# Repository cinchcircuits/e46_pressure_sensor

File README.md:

# BMW e46 pressure sensor
Boards and code for adding a pressure sensor to a BMW e46

This project adds a pressure and engine tempature readout to a BMW e46. 

# Desired install
This is the goal of the project:

The display reads out the current pressure from the installed pressure sensor, and reads \
out the engine temperature read from the CAN bus.

# Why read the temperature? 

# Board design
Find the board files [Here](board/i2c-pressure-sensor-driver)

The PCB uses the following components:
- [Teensy 4.0](https://www.pjrc.com/store/teensy40.html)
- [I2C Pressure sensor](https://www.newark.com/amphenol-advanced-sensors/npi-19m-200g2/pressure-sensor-200psi-gauge-i2c/dp/70AJ5206)
- [CAN bus tranciever](https://www.mouser.com/ProductDetail/579-MCP2562FD-E-SN)
- [wire attachment headers 4 pin](https://www.mouser.com/ProductDetail/571-1546215-4)
- [wire attachment headers 3 pin](https://www.mouser.com/ProductDetail/TE-Connectivity/282834-3?qs=A%252Bip%252BNCYi6M69kAjqV38yA%3D%3D)
- [Inexpensive "OLED" displays](https://www.amazon.com/gp/product/B08ZY4YBHL)
- [Inexpensive Amazon 3.3v relay](https://www.amazon.com/gp/product/B09P1DS8RN)
- [Shielded wire to carry the I2C](https://www.mouser.com/ProductDetail/602-M4473-100-09)

## Why an I2C pressure sensor? 

I was getting tired of dealing with analog output sensors that I was using in a different project.
So, I bought the I2C digital output sensor. It turned out to be really easy to read from.

The bad: The manufacturer lists the tread as having a M12 x 1.5 thread on it. That would be great, because that is what the sensor port on the e46 is. The problem is that these sensors actually ship with a M12 x 1.0 thread on it. 

So, I had to make an adapter for this sensor. I made it by buying one of these: [m12 to NPT adapter](https://www.amazon.com/gp/product/B08DG6YQM1)
I then threw the thing in my lathe, and cut off everything at the NPT hole and back. 
After that I bought a tap[m12 x 1.0 tap](https://www.amazon.com/gp/product/B07Z1WJ6XR)

I had to drill out the internal cavity just a bit, then I taped it and mounted the pressure sensor in the hole. Using teflon tape, and a Niton o-ring to make a seal. 

This is the result of the adapter:

## Board design

I had to rev the board once as I originally powered the 3.3v regulator off of the 12V rail, and that meant that nothing on the board got power when it wasn't plugged into an external voltage source. After moving the 3v3 regulator input to the 5V rail fixed that issue. 

I felt it was a bad idea to connect the teensy 3.3v rail to the main board 3.3v rail as that could mean that the teensy 3.3v regulator could get over currented if the relay came on when plugged into a USB connection. 

## Manufacturing the board

This time I used pcbway. They seem to have an amazing deal of $25 for a 5 boards in a 24 hour turn from China. Shipping takes a additional 5 busniess days though.

# Install

## pressure sensor install

- Start by removing the airbox
- That should give you access to the oil pressure switch, unplug it
- Unscrew the factory pressure switch
- Screw in the new pressure sensor (Perhaps with the adapter). Ideally you installed a connector in the cable unlike the way I did.
- Make some notches in the wire grommetsgoing to the DME to make room for the sensor cable

## Wire install to display

If you remove the DME completly you get access to a firewall passthrough hole in the e46, shown

Run about a meter of cable into the cabin

Pull the plastic cover off of the driver side footwell, to feed the wire through

Run the wire to the center console

You can pull on the shift boot to get at some screws to remove the center console panel

## Display mounting

I first drilled a hole in the button console where I wanted the display. Don't do that. 

Remove the button console completly from the car. 

Open the plastic, and remove the board.

Drill a hole only where you do not interfear with one of the optional buttons

You can see that I ended up breaking a connector on my board. This is okay because my car doesn't have a button in that spot

# Refernces:
- [e46 CAN bus project](https://www.bimmerforums.com/forum/showthread.php?1887229-E46-Can-bus-project)
- [ms43 DME pinout](https://www.adamomotorsport.pl/pinout-m54)
- [ms45.1 DME pinout](https://www.ms4x.net/index.php?title=Siemens_MS45_Pinout)
- [useful BMW CAN bus help](https://wiki.autosportlabs.com/BMW_E46_CAN)

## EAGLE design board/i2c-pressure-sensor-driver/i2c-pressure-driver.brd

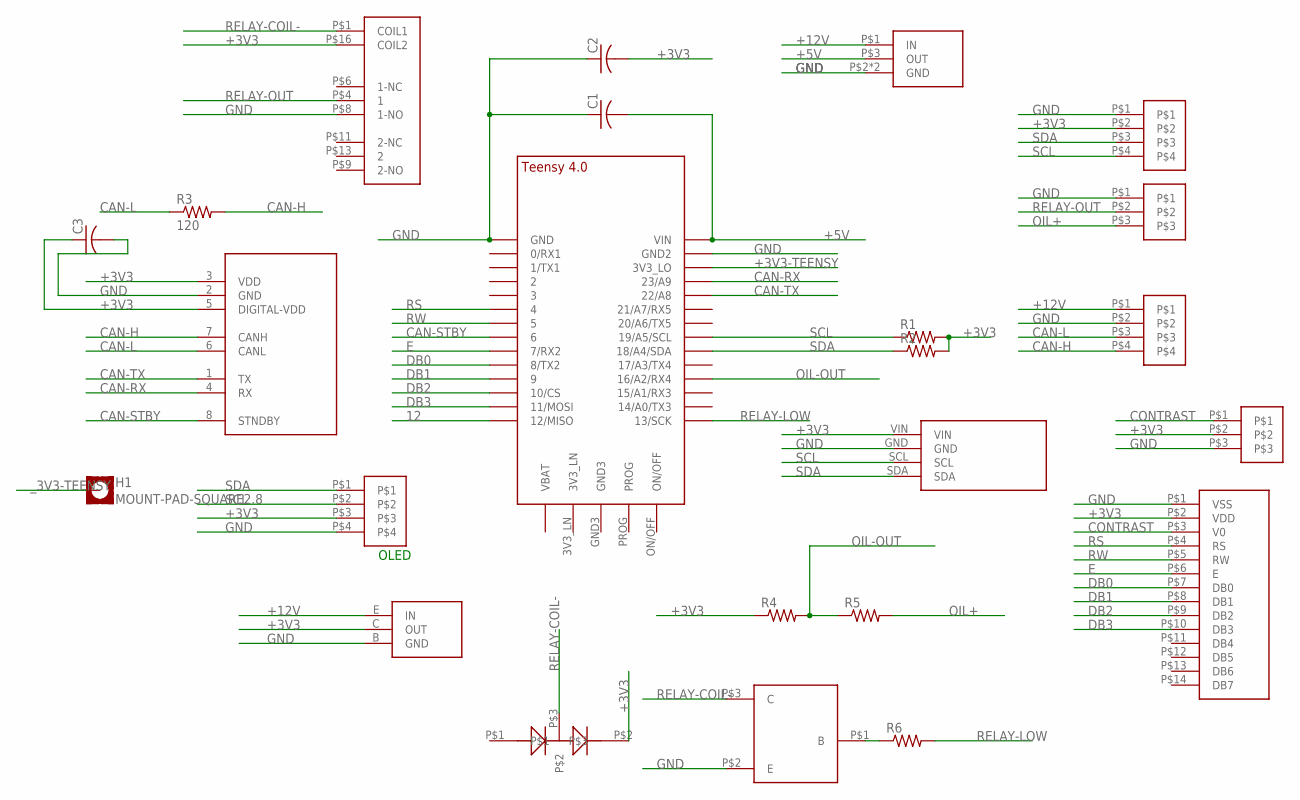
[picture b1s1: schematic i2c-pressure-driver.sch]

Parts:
C1, C2: C-USC1210K; C1210K
C3: C-USC0603K; C0603K
H1: MOUNT-PAD-SQUARE2.8; 2,8-PAD-SQUARE
R1, R2, R6: R-US_R0805; R0805
R3: 120; R0805W
R4, R5: R-US_M0805; M0805
U$1: TEENSY_4.0
U$2: NEWHAVEN-LCD-8X2; NEWHAVEN-8X2-LCD
U$3: LDO-3.3V-AZ1117CR-3.3TRG1; SOT89-BCE
U$4, U$6, U$9: 1X4-1725672
U$5: 1X3-1725669
U$7: MCP2562FD-CAN-TRANCIEVER; SOIC8
U$8: TC33X-2-102E-POT; TC33-X-2
U$10: LDO-5V-AZ1117CH2-5.0TRG1; SOT-223
U$11: BMP180-BREKOUT; BMP180-BOARD
U$12: RELAY-AMAZON; RELAY-3V-AMAZON
U$13: NPN-GENERAL; SOT23
U$14: DIODE-MMBD4148SE; SOT23

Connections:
12: U$1.12/MISO
+3V3: C2.2, C3.1, R1.2, R2.2, R4.1, U$2.P$2 (VDD), U$3.C (OUT), U$4.P$2, U$7.3 (VDD), U$7.5 (DIGITAL-VDD), U$8.P$2, U$9.P$3, U$11.VIN, U$12.P$16 (COIL2), U$14.P$2
+3V3-TEENSY: U$1.3V3_LO
+5V: C1.2, U$1.VIN, U$10.P$3 (OUT)
+12V: U$3.E (IN), U$6.P$1, U$10.P$1 (IN)
CAN-H: R3.2, U$6.P$4, U$7.7 (CANH)
CAN-L: R3.1, U$6.P$3, U$7.6 (CANL)
CAN-RX: U$1.23/A9, U$7.4 (RX)
CAN-STBY: U$1.6, U$7.8 (STNDBY)
CAN-TX: U$1.22/A8, U$7.1 (TX)
CONTRAST: U$2.P$3 (V0), U$8.P$1
DB0: U$1.8 (8/TX2), U$2.P$7 (DB0)
DB1: U$1.9/CS (9), U$2.P$8 (DB1)
DB2: U$1.10/CS, U$2.P$9 (DB2)
DB3: U$1.11/MOSI, U$2.P$10 (DB3)
E: U$1.7 (7/RX2), U$2.P$6 (E)
GND: C1.1, C2.1, C3.2, U$1.GND, U$1.GND2, U$2.P$1 (VSS), U$3.B (GND), U$4.P$1, U$5.P$1, U$6.P$2, U$7.2 (GND), U$8.P$3, U$9.P$4, U$10.P$2 (GND), U$10.PAD (GND), U$11.GND, U$12.P$8 (1-NO), U$13.P$2 (E)
unnamed: R6.1, U$13.P$1 (B)
OIL+: R5.2, U$5.P$3
OIL-OUT: R4.2, R5.1, U$1.16/A2 (16/A2/RX4)
RELAY-COIL-: U$12.P$1 (COIL1), U$13.P$3 (C), U$14.P$3
RELAY-LOW: R6.2, U$1.13/SCK
RELAY-OUT: U$5.P$2, U$12.P$4 (1)
RS: U$1.4/CANRX (4), U$2.P$4 (RS)
RW: U$1.5, U$2.P$5 (RW)
SCL: R1.1, U$1.19/A5/SCL, U$4.P$4, U$9.P$2, U$11.SCL
SDA: R2.1, U$1.18/A4/SDA, U$4.P$3, U$9.P$1, U$11.SDA
_3V3-TEENSY: H1.B2,8

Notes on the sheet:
OLED

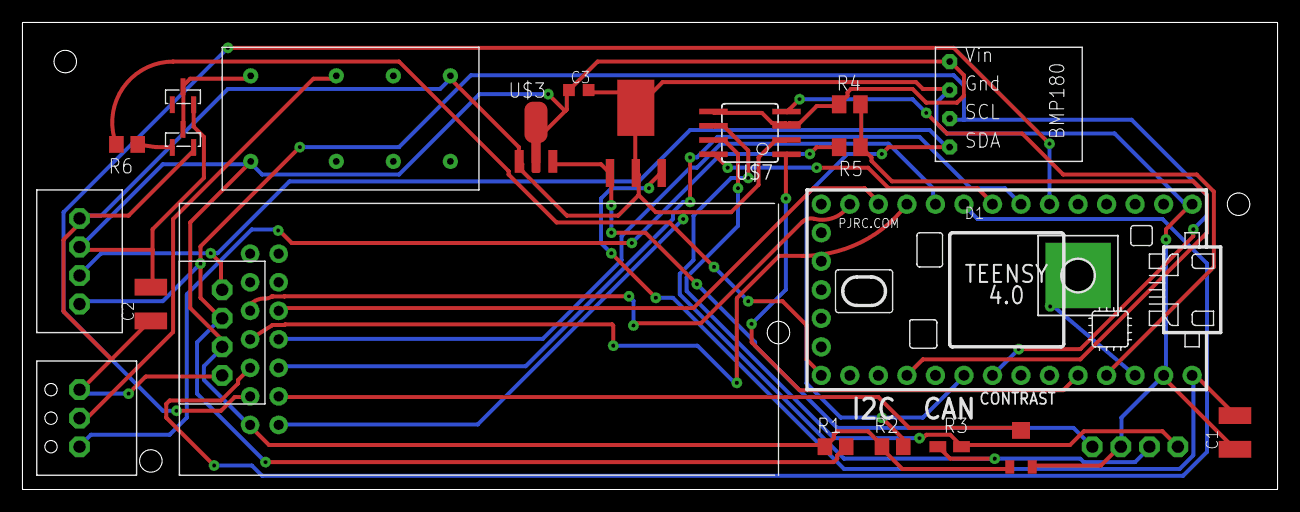
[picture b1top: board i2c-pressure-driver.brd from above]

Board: 2 copper layers, 111.7 x 41.6 mm, 24 parts (1 on the bottom side), 25 nets.

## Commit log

2023-12-29 Adding basic images to use
2023-12-29 Adding frist board files
2023-12-29 Added some reference links
2023-12-29 iAdding test image link
2023-12-29 second attempt at basic git doc formatting
2023-12-29 iMore Readme added
2023-12-29 grammer fix
